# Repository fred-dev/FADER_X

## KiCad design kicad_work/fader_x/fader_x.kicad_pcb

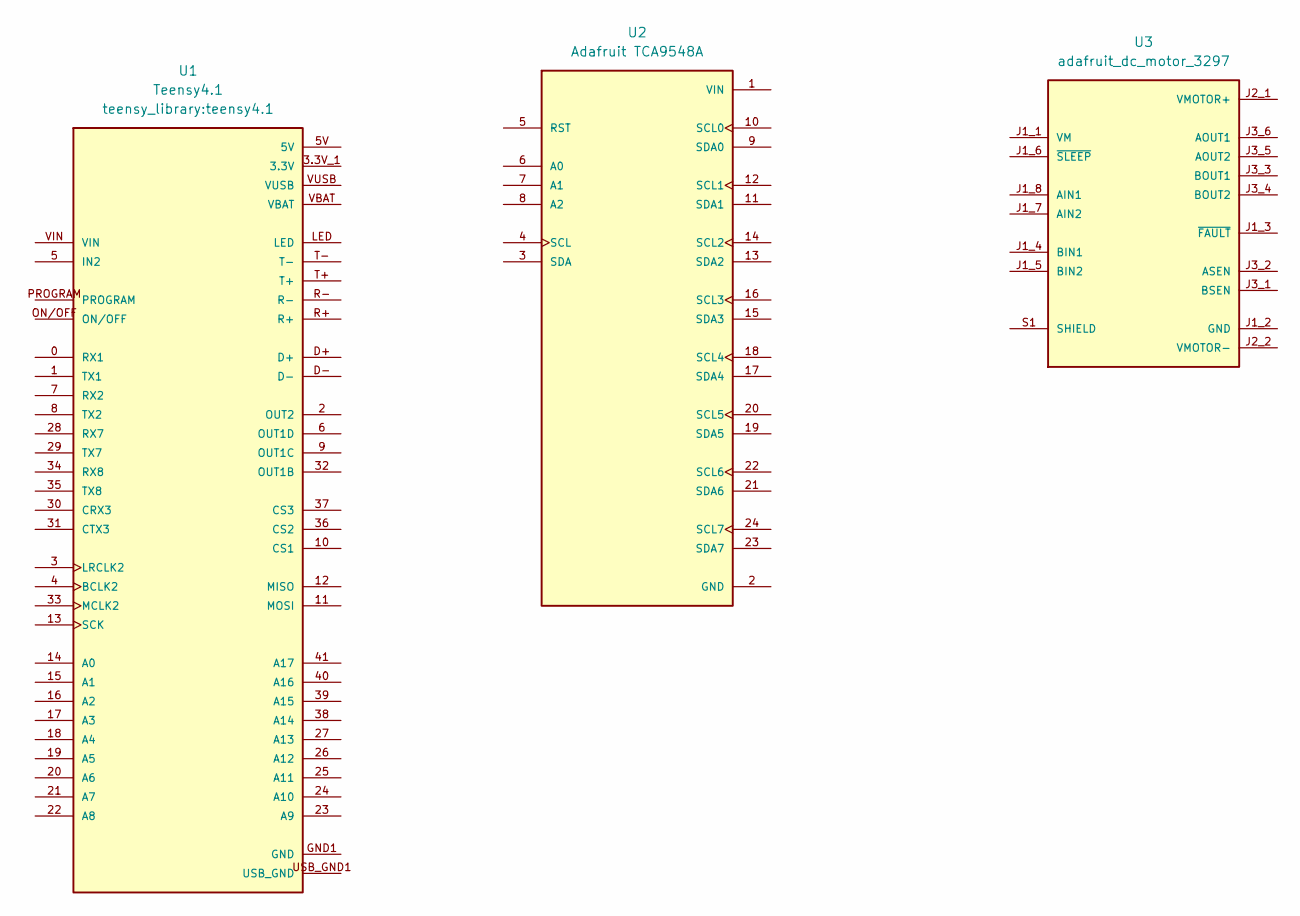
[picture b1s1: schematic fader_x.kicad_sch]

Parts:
U1: Teensy4.1; teensy4.1; PARTREV 4.1
U2: Adafruit TCA9548A; PARTREV Sep 11, 2015
U3: adafruit_dc_motor_3297; PARTREV 2020-11-20; DigiKey_Part_Number 1528-3297-ND

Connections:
3.3V: U1.3.3V_1 (3.3V), U1.3.3V_2 (3.3V), U1.3.3V_3 (3.3V)
GND: U1.GND1 (GND), U1.GND2 (GND), U1.GND3 (GND), U1.GND4 (GND), U1.GND5 (GND)
unnamed: U3.S1 (SHIELD), U3.S2 (SHIELD)
USB_GND: U1.USB_GND1 (USB_GND), U1.USB_GND2 (USB_GND)

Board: 2 copper layers, 3 parts (0 on the bottom side), 4 nets, no tracks yet.

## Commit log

2025-12-02 Add OSC test suite with working OSC message parsing
    - Created OSC.cpp and OSC.h with OSCMessage class for parsing OSC messages
    - Added tests.ino Arduino sketch that receives OSC messages on UDP port 8000
    - Fixed OSC parsing to handle standard OSC messages with type tags (e.g., ',f' for float)
    - Properly parses OSC addresses, parameter types, and float/int values
    - Forwards received OSC messages to configured destination
    - Handles both standard OSC with type tags and simplified messages without type tags
2025-12-02 Add motorized fader control to OLED test
2025-12-02 Add motorized fader control to OLED test actually
